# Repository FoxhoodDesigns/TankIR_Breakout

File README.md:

Miniature TankIR shield. Intended to be attached on top of a Arduino Nano for compact size
Components are identical to regular TANKIR schematic in regards of transistor and resistor uses.
For 5V Regulator you can use anything be it a regular 7805 (Inefficient) or one of its many drop-in replacements

Pinouts are largely the same as on Open Panzer. If you face it by its little slot in the middle: The right pin of most JST-SH connectors are the 5V. The left the GND/Open-Collector.
Servo and RC are slightly annoying. A tiny + at the corner indicates the Signal pin

Please note that this board lacks extra Servo outputs and a Button Trigger to save space. This is meant to be triggered by other control boards or (with a little bit of work on the code:) Potentially a RC Input

REVISION 2: Based on feedback. Tolerances have been greatly increased to avoid issues with fabs and accidental shorts. This new board is identified by a REV2 in the corner.

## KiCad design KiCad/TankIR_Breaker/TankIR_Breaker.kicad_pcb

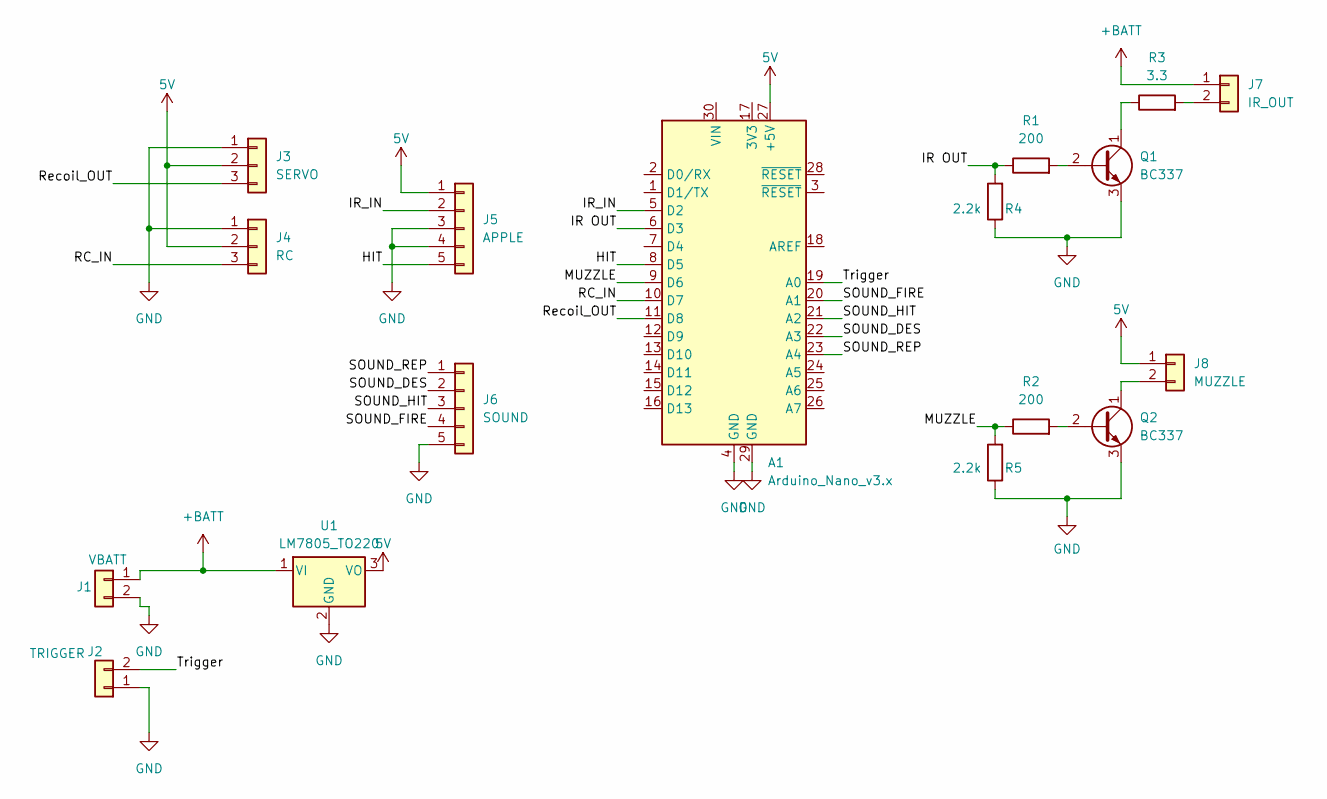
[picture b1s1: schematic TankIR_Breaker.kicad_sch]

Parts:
A1: Arduino_Nano_v3.x; Arduino_Nano
J1: VBATT; JST_PH_B2B-PH-K_1x02_P2.00mm_Vertical
J2: TRIGGER; JST_PH_B2B-PH-K_1x02_P2.00mm_Vertical
J3: SERVO; PinHeader_1x03_P2.54mm_Vertical
J4: RC; PinHeader_1x03_P2.54mm_Vertical
J5: APPLE; JST_PH_B5B-PH-K_1x05_P2.00mm_Vertical
J6: SOUND; PinHeader_1x05_P2.54mm_Vertical
J7: IR_OUT; JST_PH_B2B-PH-K_1x02_P2.00mm_Vertical
J8: MUZZLE; JST_PH_B2B-PH-K_1x02_P2.00mm_Vertical
Q1, Q2: BC337; TO-92_Inline
R1, R2: 200; R_Axial_DIN0204_L3.6mm_D1.6mm_P2.54mm_Vertical
R3: 3.3; R_Axial_DIN0204_L3.6mm_D1.6mm_P2.54mm_Vertical
R4, R5: 2.2k; R_Axial_DIN0204_L3.6mm_D1.6mm_P2.54mm_Vertical
U1: LM7805_TO220; TO-220-3_Vertical

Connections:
5V: A1.27 (+5V), J3.2, J4.2, J5.1, J8.1, U1.3 (VO)
+BATT: J1.1, J7.1, U1.1 (VI)
/HIT: A1.8 (D5), J5.5
/IR OUT: A1.6 (D3), R1.1, R4.2
/IR_IN: A1.5 (D2), J5.2
/MUZZLE: A1.9 (D6), R2.1, R5.2
/RC_IN: A1.10 (D7), J4.3
/Recoil_OUT: A1.11 (D8), J3.3
/SOUND_DES: A1.22 (A3), J6.2
/SOUND_FIRE: A1.20 (A1), J6.4
/SOUND_HIT: A1.21 (A2), J6.3
/SOUND_REP: A1.23 (A4), J6.1
/Trigger: A1.19 (A0), J2.2
GND: A1.4 (GND), A1.29 (GND), J1.2, J2.1, J3.1, J4.1, J5.3, J5.4, J6.5, Q1.3 (E), Q2.3 (E), R4.1, R5.1, U1.2 (GND)
unnamed: J7.2, R3.2
unnamed: J8.2, Q2.1 (C)
unnamed: Q1.2 (B), R1.2
unnamed: Q1.1 (C), R3.1
unnamed: Q2.2 (B), R2.2

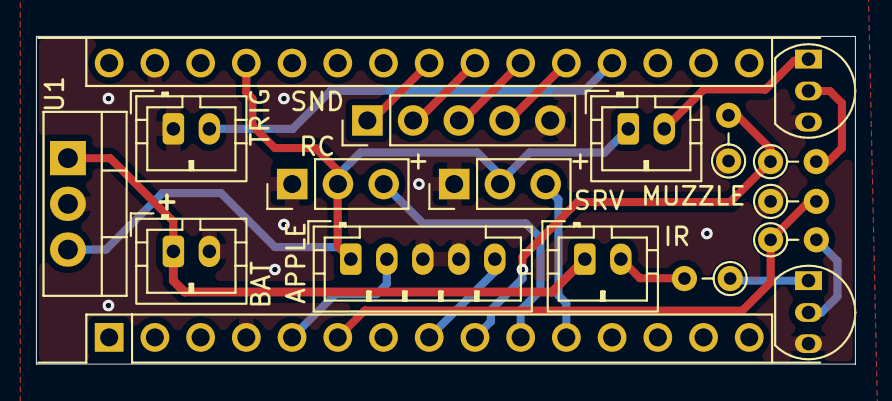
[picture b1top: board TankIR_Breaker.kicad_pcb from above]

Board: 2 copper layers, 45.5 x 18.2 mm, 17 parts (0 on the bottom side), 19 nets.

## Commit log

2026-02-19 Initial Upload
    Initial Push
2026-02-19 change
2026-02-19 fix
    Fixed missing 5V connection
2026-05-14 REV2
    Modified board for more reliable fabrication and added Pull-down resistors to avoid Transistor current leakage
2026-05-15 Correction
